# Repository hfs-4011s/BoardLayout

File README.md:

HFS 4011s PCB Design Files
=====
# Development Guide
### Software
PCB design software (EAGLE) can be downloaded [here](https://www.autodesk.com/education/free-software/eagle).

Tutorials:

[Schematic design tutorial](https://learn.sparkfun.com/tutorials/using-eagle-schematic/all)

[Creating device footprints](https://learn.sparkfun.com/tutorials/designing-pcbs-smd-footprints)

[Advanced layout](https://learn.sparkfun.com/tutorials/designing-pcbs-advanced-smd)

### Useful links
The ESP32 and USB design follows the same format as the
[HUZZAH32 ESP32 Feather](https://github.com/adafruit/Adafruit-HUZZAH32-ESP32-Feather-PCB),
so check out their [documentation](https://learn.adafruit.com/adafruit-huzzah32-esp32-feather/overview)
for programming the board using the Arduino IDE.

The battery charge design follows the same format as the [PowerBoost 500](https://github.com/adafruit/Adafruit-PowerBoost-500-Charger-PCB).
An overview can be found [here](https://learn.adafruit.com/adafruit-powerboost-500-plus-charger/overview).

# Usage
This board is meant to interface with an FPAA board developed at the Georgia
Institute of Technology and serves as part of an overall noise cancellation
pipeline meant to showcase the versatility of this technology. Our board handles
sending music and measured noise over to the FPAA, and the FPAA incorporates
our noise cancellation algorithm and sends its output to connected speakers.

This board, denoted as the HFS-4011s mainboard, includes circuitry for regulating
the battery supply voltage to 5V and 3.3V, handles charging the battery from a
micro-USB connector, and handles programming the onboard ESP32 via micro-USB.

The ESP32 is set up to connect to buttons for controlling the ANC state. A 5V
logic level SPI interface is set up and is meant to interface with LEDs to show
headphone status. The mainboard also contains a 16-bit DAC for converting the
received music to an analog signal to send over to an FPAA or speakers.

There are also a few onboard LEDs for debugging and status verification.

* `LED1` is green if the battery is fully charged
* `LED2` is orange if the battery is currently charging
* `PWR` is a power indicator LED and is blue if 5V is output from the regulator
* `LBO` is a battery status indicator LED and is red if the battery is discharged
* `D2` is a red LED connected to `GPIO13` meant for debugging

Even with solder paste, this board can be hard to assemble by hand. We ran into
a lot of problems regarding unintended shorts from the reflow process. If removing
the USB-UART bridge is necessary, the ESP32 can be programmed normally through
pins 34 and 35 (`u0RXD` and `u0TXD` respectively), but when you get to the
`Connecting...` stage, make sure the following protocol is followed:

* Short `GPIO2` and `GPIO0` to ground.
* Press the RESET button (`SW1`), which is connected to the ESP32 `EN` pin, to
momentarily reset the microcontroller. Pressing `SW1` shorts the `EN` pin to ground,
so this can be done manually as well.

After a couple of moments, the ESP32 should be flashed. The RESET button needs
to be pressed again to cycle the ESP32, and the flashed program should now run.

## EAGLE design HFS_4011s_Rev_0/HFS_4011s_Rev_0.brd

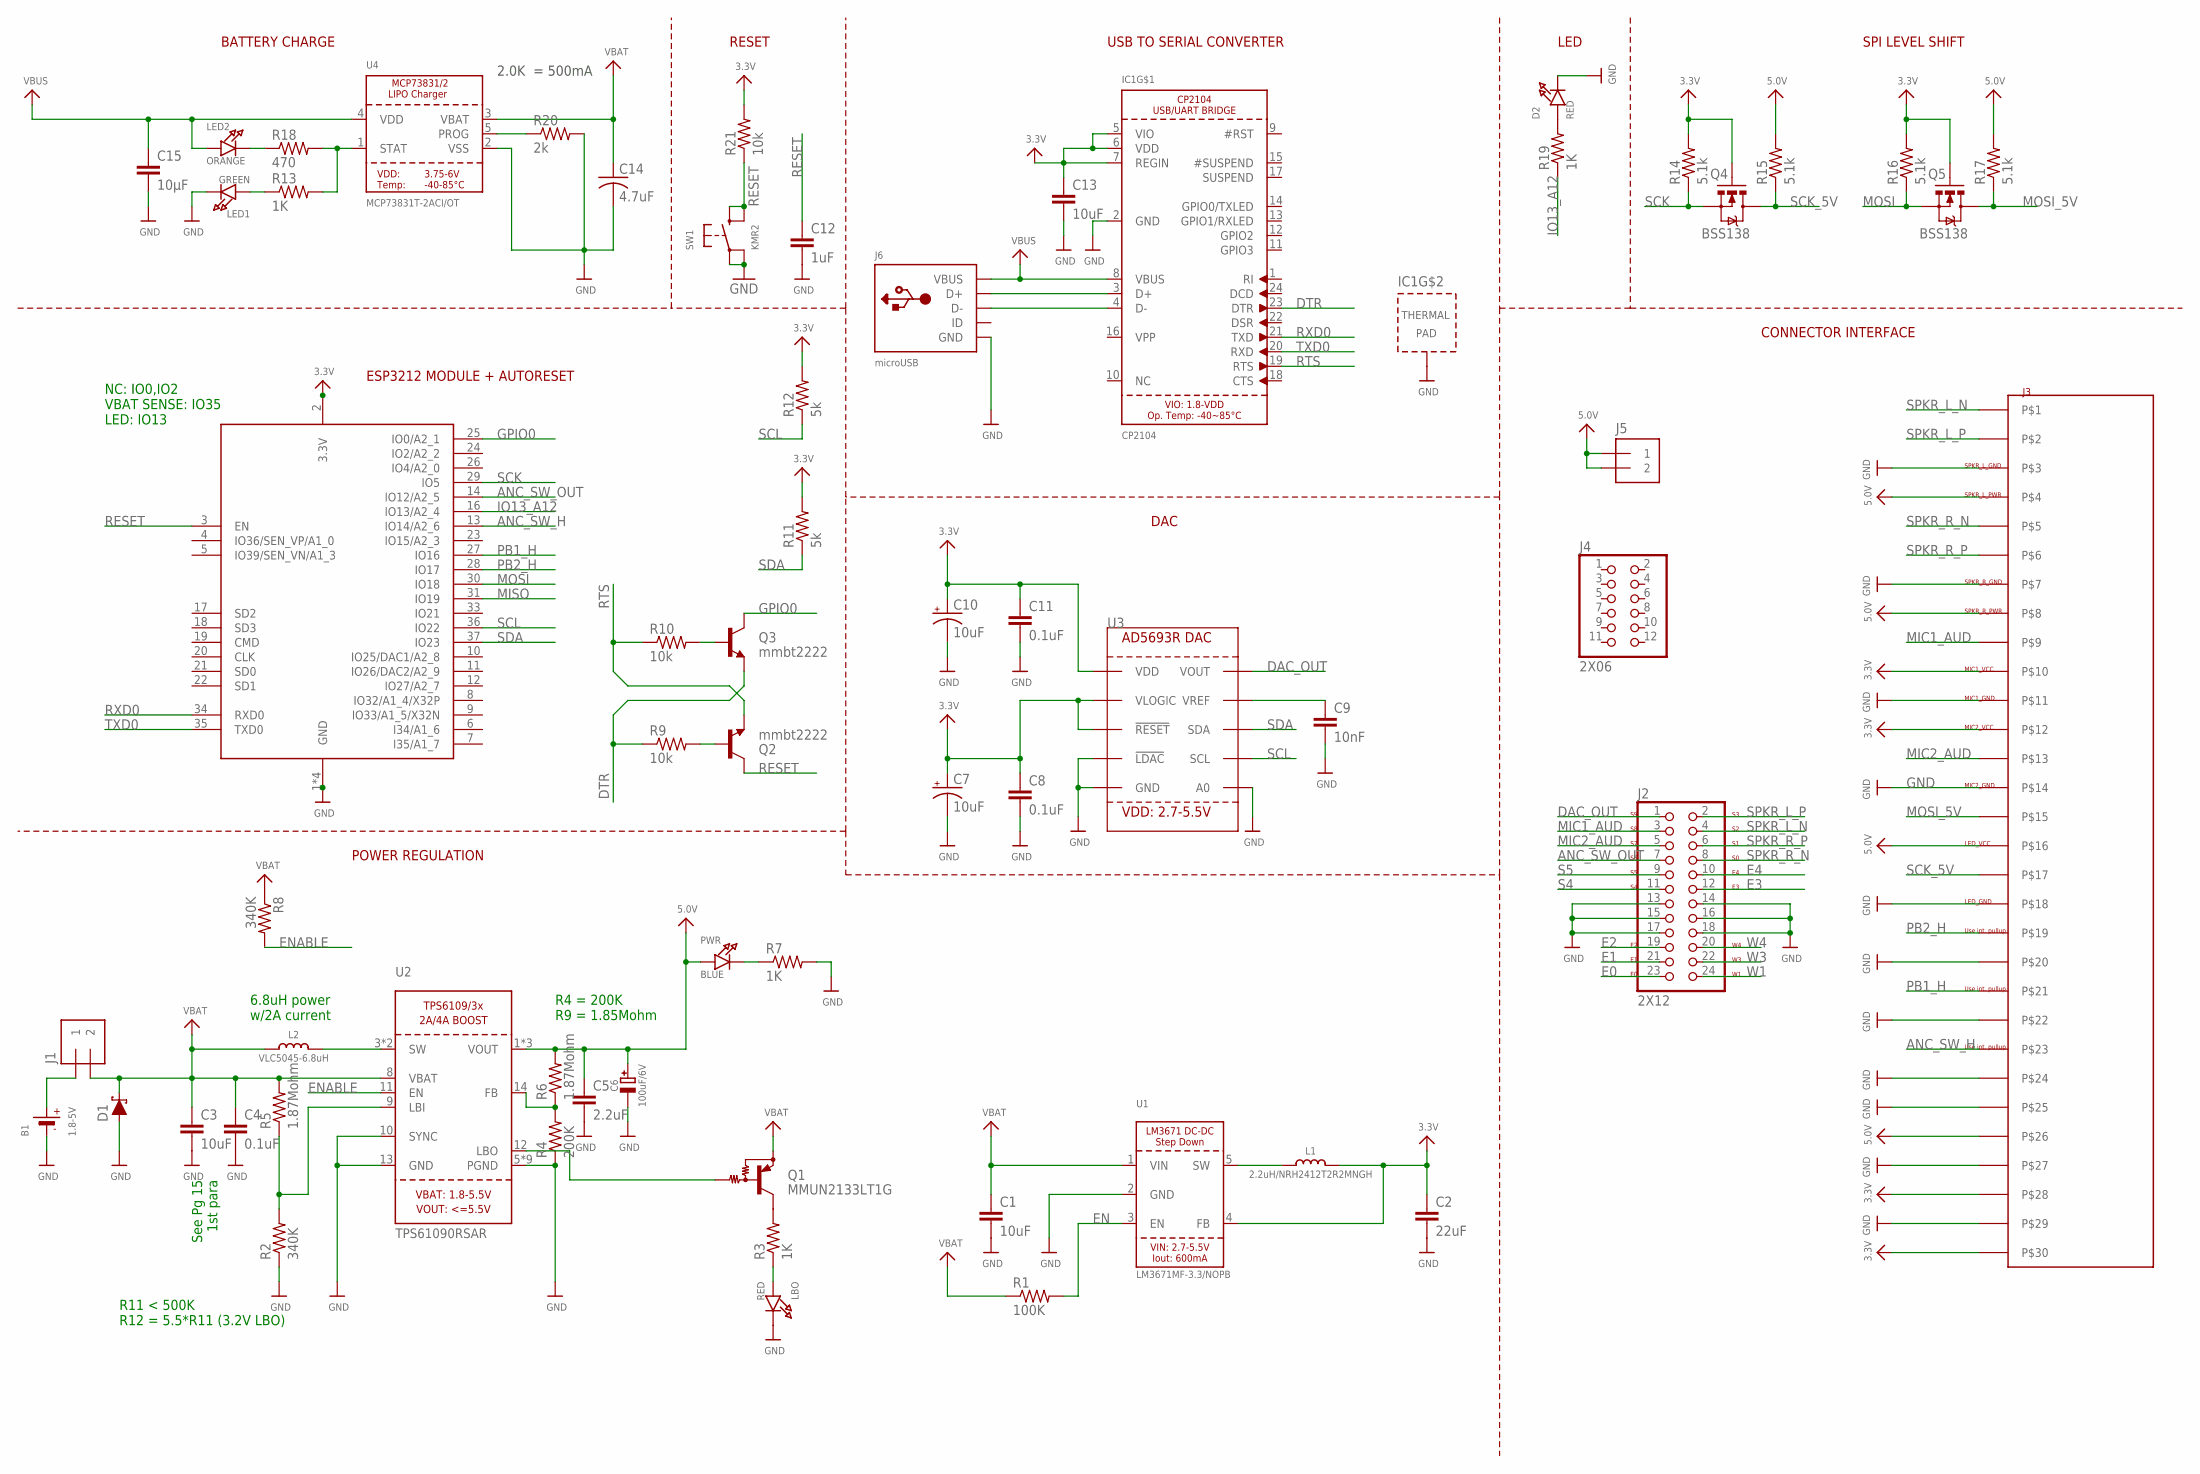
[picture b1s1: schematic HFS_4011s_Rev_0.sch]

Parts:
B1: 1.8-5V; JSTPH2
C1, C3, C13: 10uF; C0603
C2: 22uF; C0603
C4, C8, C11: 0.1uF; C0603
C5: 2.2uF; C0603
C6: 100uF/6V; EIA3528-21/B-R
C7, C10: 10uF; EIA3216
C9: 10nF; C0603
C12: 1uF; C0603
C14: 4.7uF; C1206
C15: 10µF; C0603
D1: SMAJ5.0CALFDKR-ND; DO-214AC
D2: RED; CHIPLED_0805_NOOUTLINE
IC1: CP2104; QFN24_4MM_SMSC
J1, J5: 1X02
J2: 2X12
J3: MOLEX_IGRID_15X2CONNECTOR; MOLEX_IGRID15X2CONNECTOR
J4: 2X06
J6: microUSB; 4UCONN_20329
L1: 2.2uH/NRH2412T2R2MNGH; INDUCTOR_TAIYOYUDEN_NRH2412T
L2: VLC5045-6.8uH; INDUCTOR_5X5MM_TDK_VLC5045
LBO: RED; CHIPLED_0805_NOOUTLINE
LED1: GREEN; CHIPLED_0805_NOOUTLINE
LED2: ORANGE; CHIPLED_0805_NOOUTLINE
PWR: BLUE; CHIPLED_0805_NOOUTLINE
Q1: MMUN2133LT1G; SC59-BEC
Q2, Q3: mmbt2222; SOT23-3
Q4, Q5: BSS138; SOT23-3
R1: 100K; R0603
R2, R8: 340K; R0603
R3, R7, R13, R19: 1K; R0603
R4: 200K; R0603
R5, R6: 1.87Mohm; R0603
R9, R10, R21: 10k; R0603
R11, R12: 5k; R0603
R14, R15, R16, R17: 5.1k; R0603
R18: 470; R0603
R20: 2k; R0603
SW1: KMR2; BTN_KMR2_4.6X2.8
U1: LM3671MF-3.3/NOPB; SOT23-5
U2: TPS61090RSAR; PVQFN-16
U3: AD5693R; MSOP10
U4: MCP73831T-2ACI/OT; SOT23-5
X1: ESP32_WROOM32_SKINNY; WROOM32_SKINNY

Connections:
3.3V: C2.1, C7.A (+), C8.1, C10.A (+), C11.1, C13.1, IC1.5 (VIO), IC1.6 (VDD), IC1.7 (REGIN), J3.P$10, J3.P$12, J3.P$28, J3.P$30, L1.2, Q4.1 (G), Q5.1 (G), R11.2, R12.2, R14.2, R16.2, R21.2, U1.4 (FB), U3.1 (VDD), U3.2 (VLOGIC), U3.3 (!RESET!), X1.2 (3.3V)
5.0V: C5.1, C6.+, J3.P$4, J3.P$8, J3.P$16, J3.P$26, J5.1, J5.2, PWR.A, R6.2, R15.2, R17.2, U2.1 (VOUT), U2.15 (VOUT), U2.16 (VOUT)
ANC_SW_H: J3.P$23, X1.13 (IO14/A2_6)
ANC_SW_OUT: J2.7, X1.14 (IO12/A2_5)
DAC_OUT: J2.1, U3.10 (VOUT)
DTR: IC1.23 (DTR), Q3.2 (E), R9.1
E0: J2.23
E1: J2.21
E2: J2.19
E3: J2.12
E4: J2.10
EN: R1.2, U1.3 (EN)
ENABLE: R8.2, U2.11 (EN)
GND: B1.1 (-), C1.2, C2.2, C3.2, C4.2, C5.2, C6.-, C7.C (-), C8.2, C9.2, C10.C (-), C11.2, C12.2, C13.2, C14.2, C15.2, D1.A, D2.C, IC1.2 (GND), IC1.THERM (TP), J2.13, J2.14, J2.15, J2.16, J2.17, J2.18, J3.P$3, J3.P$7, J3.P$11, J3.P$14, J3.P$18, J3.P$20, J3.P$22, J3.P$24, J3.P$25, J3.P$27, J3.P$29, J6.BASE@1 (GND), J6.BASE@2 (GND), J6.GND, J6.SPRT@1 (GND), J6.SPRT@2 (GND), J6.SPRT@3 (GND), J6.SPRT@4 (GND), LBO.C, LED1.C, R2.1, R4.1, R7.2, R20.2, SW1.A, SW1.A' (P1), U1.2 (GND), U2.5 (PGND), U2.6 (PGND), U2.7 (PGND), U2.10 (SYNC), U2.13 (GND), U2.P$18 (PGND), U2.P$19 (PGND), U2.P$20 (PGND), U2.P$21 (PGND), U2.P$22 (PGND), U2.THERMAL (PGND), U3.4 (!LDAC!), U3.5 (GND), U3.6 (A0), U4.2 (VSS), X1.1 (GND), X1.15 (GND), X1.38 (GND), X1.P$1 (GND)
GPIO0: Q3.3 (C), X1.25 (IO0/A2_1)
IO13_A12: R19.1, X1.16 (IO13/A2_4)
LBO: Q1.B, U2.12 (LBO)
MIC1_AUD: J2.3, J3.P$9
MIC2_AUD: J2.5, J3.P$13
MISO: X1.31 (IO19)
MOSI: Q5.2 (S), R16.1, X1.30 (IO18)
MOSI_5V: J3.P$15, Q5.3 (D), R17.1
unnamed: LED2.C, R18.1
unnamed: IC1.3 (D+), J6.D+
unnamed: L2.P$2 (2), U2.3 (SW), U2.4 (SW)
unnamed: R2.2, R5.1, U2.9 (LBI)
unnamed: D2.A, R19.2
unnamed: IC1.4 (D-), J6.D-
unnamed: R13.2, R18.2, U4.1 (STAT)
unnamed: R20.1, U4.5 (PROG)
unnamed: LED1.A, R13.1
unnamed: PWR.C, R7.1
unnamed: R4.2, R6.1, U2.14 (FB)
unnamed: Q2.1 (B), R9.2
unnamed: Q3.1 (B), R10.2
unnamed: LBO.A, R3.1
unnamed: Q1.C, R3.2
unnamed: B1.2 (+), J1.1
unnamed: L1.1, U1.5 (SW)
unnamed: C9.1, U3.9 (VREF)
PB1_H: J3.P$21, X1.27 (IO16)
PB2_H: J3.P$19, X1.28 (IO17)
RESET: C12.1, Q2.3 (C), R21.1, SW1.B (S), SW1.B' (S1), X1.3 (EN)
RTS: IC1.19 (RTS), Q2.2 (E), R10.1
RXD0: IC1.21 (TXD), X1.34 (RXD0)
S4: J2.11
S5: J2.9
SCK: Q4.2 (S), R14.1, X1.29 (IO5)
SCK_5V: J3.P$17, Q4.3 (D), R15.1
SCL: R12.1, U3.7 (SCL), X1.36 (IO22)
SDA: R11.1, U3.8 (SDA), X1.37 (IO23)
SPKR_L_N: J2.4, J3.P$1
SPKR_L_P: J2.2, J3.P$2
SPKR_R_N: J2.8, J3.P$5
SPKR_R_P: J2.6, J3.P$6
TXD0: IC1.20 (RXD), X1.35 (TXD0)
VBAT: C1.1, C3.1, C4.1, C14.1, D1.C, J1.2, L2.P$1 (1), Q1.E, R1.1, R5.2, R8.1, U1.1 (VIN), U2.8 (VBAT), U4.3 (VBAT)
VBUS: C15.1, IC1.8 (VBUS), J6.VBUS, LED2.A, U4.4 (VDD)
W1: J2.24
W3: J2.22
W4: J2.20

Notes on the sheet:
RESET
USB TO SERIAL CONVERTER
LED
ESP3212 MODULE + AUTORESET
NC: IO0,IO2 VBAT SENSE: IO35 LED: IO13
2.0K = 500mA
See Pg 15 1st para
6.8uH power w/2A current
R11 < 500K R12 = 5.5*R11 (3.2V LBO)
R4 = 200K R9 = 1.85Mohm
BATTERY CHARGE
POWER REGULATION
DAC
LED_VCC
LED_GND
MIC1_VCC
MIC1_GND
MIC2_GND
MIC2_VCC
SPKR_L_PWR
SPKR_R_PWR
SPKR_R_GND
SPKR_L_GND
Use int. pullup
SPI LEVEL SHIFT
CONNECTOR INTERFACE

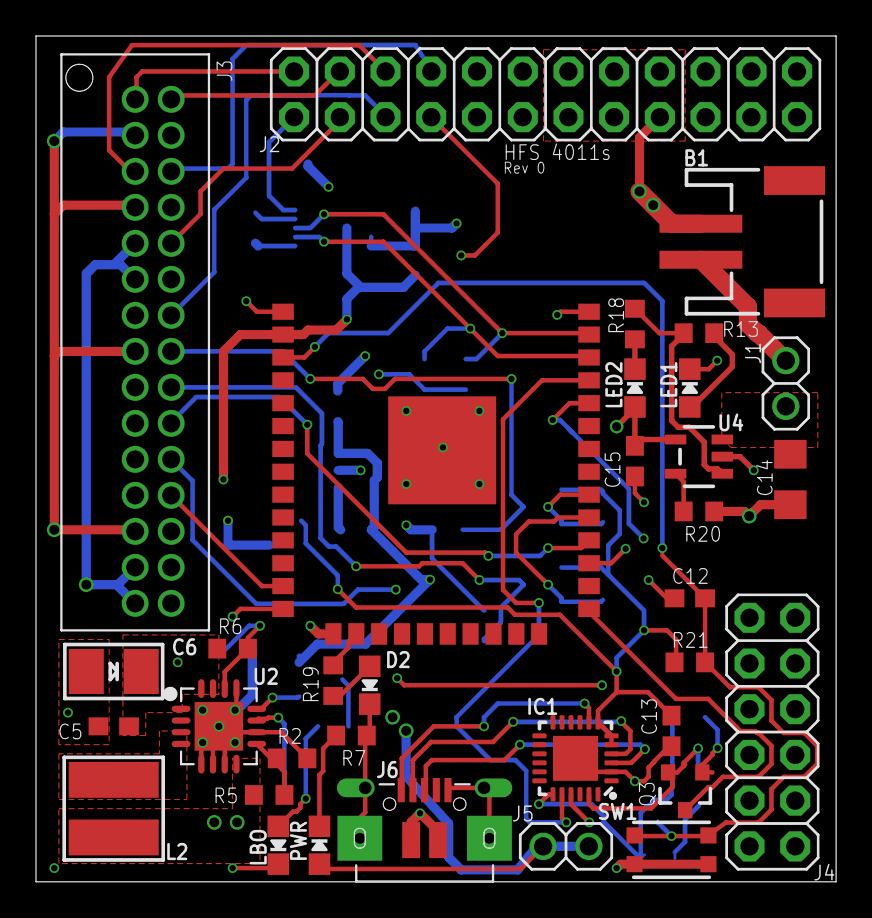
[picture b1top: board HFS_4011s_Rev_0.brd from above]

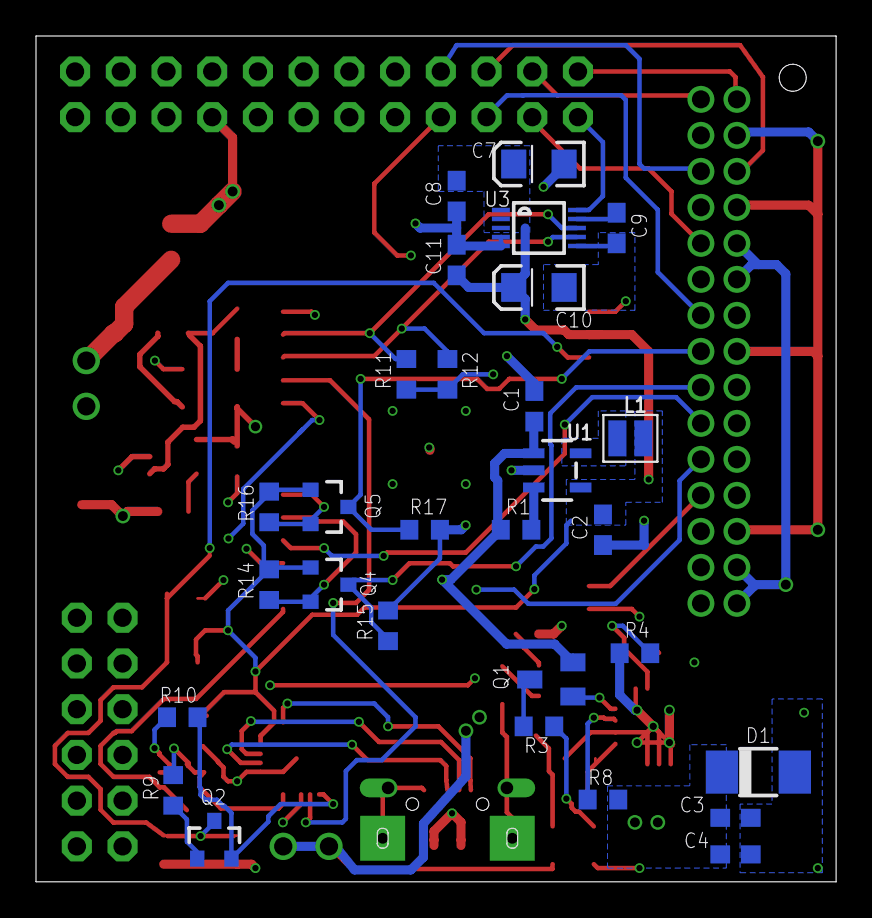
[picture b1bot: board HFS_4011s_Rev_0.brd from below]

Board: 4 copper layers, 44.5 x 47.0 mm, 63 parts (29 on the bottom side), 50 nets.

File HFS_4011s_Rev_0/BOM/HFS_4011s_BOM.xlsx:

Part | Value | Device | Package | Description | Quantity | Price 1 | Manufacturer_ID | Link 1 | Alternate ID | Alternate Link
B1 | 1.8-5V | BATTERY | JSTPH2 | CR1220 SMT - Digikey: 3001K-ND | 1 | 19.95 | ICR18650 | https://www.digikey.com/product-detail/en/adafruit-industrie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
C1, C3, C13, C15 | 10uF | C-EUC0603 | C0603 | CAPACITOR, European symbol | 4 | 0.21 | GRM188R61A106KE69D | https://www.digikey.com/product-detail/en/murata-electronics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 | JMK107BJ106MA-T | https://www.digikey.com/product-detail/en/taiyo-yuden/JMK107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
C12 | 1uF | C-EUC0603 | C0603 | CAPACITOR, European symbol | 1 | 0.1 | CL10A105KP8NNNC | https://www.digikey.com/product-detail/en/samsung-electro-me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 | CL10A105KQ8NNNC | https://www.digikey.com/product-detail/en/samsung-electro-me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
C14 | 4.7uF | C-USC1206 | C1206 | CAPACITOR, American symbol | 1 | 0.26 | CL31B475KAHNNWE | https://www.digikey.com/product-detail/en/samsung-electro-me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 | CL31A475KOHNNNE | https://www.digikey.com/product-detail/en/samsung-electro-me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
C2 | 22uF | C-EUC0603 | C0603 | CAPACITOR, European symbol | 1 | 0.31 | GRM188R61A226ME15D | https://www.digikey.com/product-detail/en/murata-electronics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 | CL10A226MQ8NRNE | https://www.digikey.com/product-detail/en/samsung-electro-me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
C4, C8, C11 | 0.1uF | C-EUC0603 | C0603 | CAPACITOR, European symbol | 3 | 0.1 | CL10B104KB8NNNC | https://www.digikey.com/product-detail/en/samsung-electro-me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 | CL10B104KO8NNNC | https://www.digikey.com/product-detail/en/samsung-electro-me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
C5 | 2.2uF | C-EUC0603 | C0603 | CAPACITOR, European symbol | 1 | 0.11 | CL10A225KP8NNNC | https://www.digikey.com/product-detail/en/samsung-electro-me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 | CL10A225KQ8NNNC | https://www.digikey.com/product-detail/en/samsung-electro-me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
C6 | 100uF/6V | CAP_TANTALUMB/3528_REFLOW | EIA3528-21/B-R | Tantalum Capacitors | 1 | 0.65 | TPSB107K006R0250 | https://www.digikey.com/product-detail/en/avx-corporation/TP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 | TPSB107M006R0250 | https://www.digikey.com/product-detail/en/avx-corporation/TP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
C7, C10 | 10uF | 10UF-TANT | EIA3216 | 10uF Tantalum SMT | 2 | 0.41 | TPSA106K010R0900 | https://www.digikey.com/product-detail/en/avx-corporation/TP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 | TPSA106M010R0900 | https://www.digikey.com/product-detail/en/avx-corporation/TP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
C9 | 10nF | C-EUC0603 | C0603 | CAPACITOR, European symbol | 1 | 0.1 | CL10B103KB8NNNC | https://www.digikey.com/product-detail/en/samsung-electro-me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 | CL10B103KB8NCNC | https://www.digikey.com/product-detail/en/samsung-electro-me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
D1 | SMAJ5.0CALFDKR-ND | SMAJ5.0CALFDKR-ND | DO-214AC | TVS Diode | 1 | 0.47 | SMAJ5.0CA | https://www.digikey.com/product-detail/en/littelfuse-inc/SMA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
D2, LBO | RED | LED0805_NOOUTLINE | CHIPLED_0805_NOOUTLINE | LED | 1 | 0.31 | LTST-C171KRKT | https://www.digikey.com/product-detail/en/lite-on-inc/LTST-C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 | LTST-C170KRKT | https://www.digikey.com/product-detail/en/lite-on-inc/LTST-C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
IC1 | CP2104 | CP2104 | QFN24_4MM_SMSC | CP2104 - USB to UART Bridge | 1 | 1.65 | CP2104-F03-GMR | https://www.digikey.com/product-detail/en/silicon-labs/CP210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
J1 | 1X02 | 1X02 | 1X02 | Power Switch | 1 | 1.5 | SPDT Switch (no product ID given) | https://www.sparkfun.com/products/102
J2, J4, J5 | 2x23 Stacking Headers | 2x23 | 2x23 | 2 pack of 2x23 Stacking header pins | 1 | 4.95 | 706 | https://www.adafruit.com/product/706
 |  | Molex_Socket_Contact |  | Socket contacts for iGrid connector (50 cost 7.18) | 50 | 0.21 | 5016471100 | https://www.digikey.com/product-detail/en/molex/5016471100/W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
J3 |  | MOLEX_IGRID_15X2CONNECTOR | MOLEX_IGRID15X2CONNECTOR |  | 1 | 2.54 | 501645-3020 | https://www.digikey.com/product-detail/en/molex/501645-3020/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
J6 | microUSB | USBMICRO_20329 | 4UCONN_20329 | USB Connectors | 1 | 0.78 | 10103592-0001LF | https://www.digikey.com/product-detail/en/amphenol-icc-fci/1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
L1 | 2.2uH/NRH2412T2R2MNGH | INDUCTORNRH2412T | INDUCTOR_TAIYOYUDEN_NRH2412T | Inductors | 1 | 0.23 | NRH2412T2R2MNGH | https://www.digikey.com/product-detail/en/taiyo-yuden/NRH241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
L2 | VLC5045-6.8uH | INDUCTORTDK_VLC5045 | INDUCTOR_5X5MM_TDK_VLC5045 | Inductors (schematic version is obsolete) | 1 | 0.48 | VLS5045EX-6R8M | https://www.digikey.com/product-detail/en/tdk-corporation/VL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
LED1 | GREEN | LED0805_NOOUTLINE | CHIPLED_0805_NOOUTLINE | LED | 1 | 0.31 | LTST-C171KGKT | https://www.digikey.com/product-detail/en/lite-on-inc/LTST-C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 | LTST-C171GKT | https://www.digikey.com/product-detail/en/lite-on-inc/LTST-C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
LED2 | ORANGE | LED0805_NOOUTLINE | CHIPLED_0805_NOOUTLINE | LED | 1 | 0.31 | LTST-C170KFKT | https://www.digikey.com/product-detail/en/lite-on-inc/LTST-C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 | LTST-C171AKT | https://www.digikey.com/product-detail/en/lite-on-inc/LTST-C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
PWR | BLUE | LED0805_NOOUTLINE | CHIPLED_0805_NOOUTLINE | LED | 1 | 0.51 | LTST-C171TBKT | https://www.digikey.com/product-detail/en/lite-on-inc/LTST-C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 | LTST-C170TBKT | https://www.digikey.com/product-detail/en/lite-on-inc/LTST-C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
Q1 | MMUN2133LT1G | MUN2114T1-PNP_DRIVER-SC59-BEC | SC59-BEC | PNP Bias Resistor Transistor
Q2, Q3 | mmbt2222 | TRANSISTOR_NPNSOT23-3 | SOT23-3 | Transistor NPN
Q4, Q5 | BSS138 | MOSFET-NCHANNELSMD | SOT23-3
R1 | 100K | R-US_R0603 | R0603 | RESISTOR, American symbol
R11, R12 | 5k | R-US_R0603 | R0603 | RESISTOR, American symbol
R14, R15, R16, R17 | 5.1k | R-US_R0603 | R0603 | RESISTOR, American symbol
R18 | 470 | R-US_R0603 | R0603 | RESISTOR, American symbol
R2, R8 | 340K | R-US_R0603 | R0603 | RESISTOR, American symbol
R20 | 2k | R-US_R0603 | R0603 | RESISTOR, American symbol
R3, R7, R13, R19 | 1K | R-US_R0603 | R0603 | RESISTOR, American symbol
R4 | 200K | R-US_R0603 | R0603 | RESISTOR, American symbol
R5, R6 | 1.87Mohm | R-US_R0603 | R0603 | RESISTOR, American symbol
R9, R10, R21 | 10k | R-US_R0603 | R0603 | RESISTOR, American symbol
SW1 | KMR2 | SWITCH_TACT_SMT4.6X2.8 | BTN_KMR2_4.6X2.8 | SMT Tact Switches
U1 | LM3671MF-3.3/NOPB | VREG_LM3671 | SOT23-5 | LM3671 - 600mA DC-DC Step-Down Converter
U2 | TPS61090RSAR | VREG_TPS6103X | PVQFN-16 | TPS6103x 4A Boost - 1.8-5.5V Input, Adjustable Output to 5.5V
U3 | AD5693R | AD5693R | MSOP10
U4 | MCP73831T-2ACI/OT | MCP73831/2 | SOT23-5 | MCP73831/2 LIPO Charger
X1 | ESP32_WROOM32_SKINNY | ESP32_WROOM32_SKINNY | WROOM32_SKINNY
 | 1x36 Pin Headers |  |  | 10 pack of 1x36 header pins | 1 | 4.95 | 3009 | https://www.adafruit.com/product/3009
Add peripherals here
 |  |  |  |  | Totals | 52.93

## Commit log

2019-02-08 First commit. Added readme with tutorials for board design.
2019-02-08 Fixed hyperlinks in readme.
2019-03-02 Started board design. Added necessary components for programming esp32, and added some useful libraries.
2019-03-03 Added power circuitry to board. Using 5V buck boost and 3.3V LDO. Added 1x02 pin header for on-off switch.
2019-03-03 Added TVS diode on battery, and moved switch to battery.
2019-03-03 Cleaned up schematic and added ground planes.
2019-03-04 Added in 3.3V buck converter and got rid of 3.3V LDO.
2019-03-04 Created pdfs of board and schematic.
2019-03-10 Added in DAC
2019-03-10 Added labels for FPAA IO. Still determining peripherals.
2019-03-10 Working on IO. Need to get bigger connector for IO!
2019-03-11 Addded peripherals. Still need to connect IO from microcontroller to connector.
2019-03-11 Updated board and schematic pdfs.
2019-03-12 Started board layout. Placed battery charge circuitry, usb-serial conversion, and reset components onto board.
2019-03-18 Changed usb C back to micro usb. Converted board to a 4-layer design. Routed 5V power supply.
2019-03-18 Moved esp32 board up a little and added debug LED.
2019-03-19 All components on board. Need to finish routing some signals to connectors.
2019-03-19 Routed all components (0 airwire errors). But getting a lot of clearance errors. Also changed connector pinout
2019-03-19 Renumbered components and fixing DRC errors.
2019-03-20 Finished adding all silkscreen text. Got rid of some clearance errors. Seems like everything is set for fab.
2019-03-20 Added board title text to silkscreen and added osh images to repo.
2019-03-20 Updated pdfs
2019-03-25 Updated readme with links to adafruit boards for reference.
2019-03-25 Reformatted readme.
2019-03-25 Adding gerbers to repo and working on BOM.
2019-04-30 Adding BOM used to order components.
2019-04-30 Wrote notes on how to use the board.
2019-04-30 Added descriptors for pins.
2019-04-30 Missed a descriptor.

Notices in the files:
parts and their libraries:
microbuilder: This work is placed in the public domain, and may be freely used for commercial and non-commercial work with the following conditions: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
SparkFun: Licensing: CC v3.0 Share-Alike You are welcome to use this library for commercial purposes.
